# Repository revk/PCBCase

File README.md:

# PCBCase

Now at [Codeberg](https://codeberg.org/RevK/PCBCase)

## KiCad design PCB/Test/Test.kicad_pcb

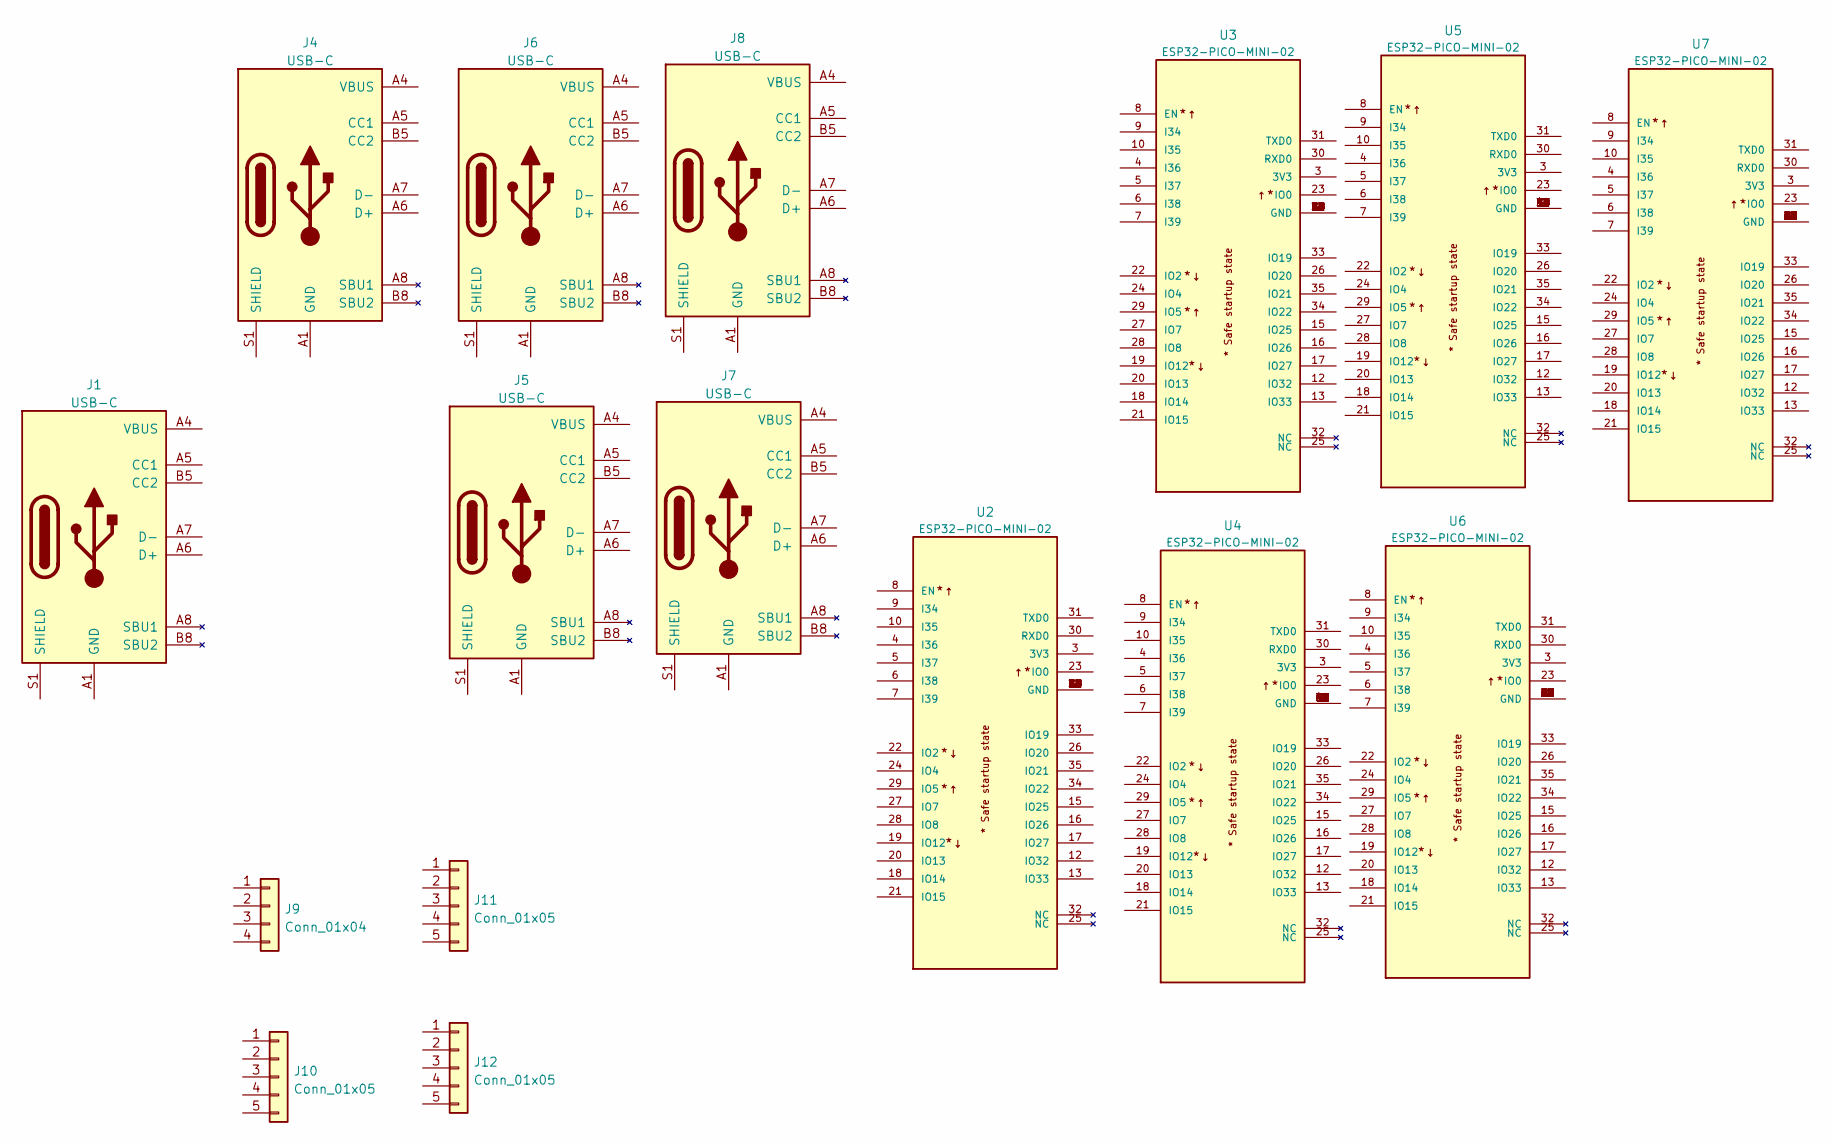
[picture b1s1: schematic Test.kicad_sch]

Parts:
J1, J4, J5, J6, J7, J8: USB-C; USC16-TR-Round
J9: Conn_01x04; JLC-PinHeader_1x04_P2.54mm_Right
J10: Conn_01x05; PTSM-HH-5-RA-P
J11: Conn_01x05; PTSM-HH-5-RA
J12: Conn_01x05; PTSM-HH-5-RA-P-SMD
U2, U3, U4, U5, U6, U7: ESP32-PICO-MINI-02; PARTREV v1.0

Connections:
unnamed: J1.A1 (GND), J1.A12 (GND), J1.B1 (GND), J1.B12 (GND)
unnamed: J1.A4 (VBUS), J1.A9 (VBUS), J1.B4 (VBUS), J1.B9 (VBUS)
unnamed: J1.A6 (D+), J1.B6 (D+)
unnamed: J1.A7 (D-), J1.B7 (D-)
unnamed: J4.A1 (GND), J4.A12 (GND), J4.B1 (GND), J4.B12 (GND)
unnamed: J4.A4 (VBUS), J4.A9 (VBUS), J4.B4 (VBUS), J4.B9 (VBUS)
unnamed: J4.A6 (D+), J4.B6 (D+)
unnamed: J4.A7 (D-), J4.B7 (D-)
unnamed: J5.A1 (GND), J5.A12 (GND), J5.B1 (GND), J5.B12 (GND)
unnamed: J5.A4 (VBUS), J5.A9 (VBUS), J5.B4 (VBUS), J5.B9 (VBUS)
unnamed: J5.A6 (D+), J5.B6 (D+)
unnamed: J5.A7 (D-), J5.B7 (D-)
unnamed: J6.A1 (GND), J6.A12 (GND), J6.B1 (GND), J6.B12 (GND)
unnamed: J6.A4 (VBUS), J6.A9 (VBUS), J6.B4 (VBUS), J6.B9 (VBUS)
unnamed: J6.A6 (D+), J6.B6 (D+)
unnamed: J6.A7 (D-), J6.B7 (D-)
unnamed: J7.A1 (GND), J7.A12 (GND), J7.B1 (GND), J7.B12 (GND)
unnamed: J7.A4 (VBUS), J7.A9 (VBUS), J7.B4 (VBUS), J7.B9 (VBUS)
unnamed: J7.A6 (D+), J7.B6 (D+)
unnamed: J7.A7 (D-), J7.B7 (D-)
unnamed: J8.A1 (GND), J8.A12 (GND), J8.B1 (GND), J8.B12 (GND)
unnamed: J8.A4 (VBUS), J8.A9 (VBUS), J8.B4 (VBUS), J8.B9 (VBUS)
unnamed: J8.A6 (D+), J8.B6 (D+)
unnamed: J8.A7 (D-), J8.B7 (D-)
unnamed: U2.1 (GND), U2.2 (GND), U2.11 (GND), U2.14 (GND), U2.36 (GND), U2.37 (GND), U2.38 (GND), U2.39 (GND), U2.40 (GND), U2.41 (GND), U2.42 (GND), U2.43 (GND), U2.44 (GND), U2.45 (GND), U2.46 (GND), U2.47 (GND), U2.48 (GND), U2.49 (GND), U2.50 (GND), U2.51 (GND), U2.52 (GND), U2.53 (GND)
unnamed: U3.1 (GND), U3.2 (GND), U3.11 (GND), U3.14 (GND), U3.36 (GND), U3.37 (GND), U3.38 (GND), U3.39 (GND), U3.40 (GND), U3.41 (GND), U3.42 (GND), U3.43 (GND), U3.44 (GND), U3.45 (GND), U3.46 (GND), U3.47 (GND), U3.48 (GND), U3.49 (GND), U3.50 (GND), U3.51 (GND), U3.52 (GND), U3.53 (GND)
unnamed: U4.1 (GND), U4.2 (GND), U4.11 (GND), U4.14 (GND), U4.36 (GND), U4.37 (GND), U4.38 (GND), U4.39 (GND), U4.40 (GND), U4.41 (GND), U4.42 (GND), U4.43 (GND), U4.44 (GND), U4.45 (GND), U4.46 (GND), U4.47 (GND), U4.48 (GND), U4.49 (GND), U4.50 (GND), U4.51 (GND), U4.52 (GND), U4.53 (GND)
unnamed: U5.1 (GND), U5.2 (GND), U5.11 (GND), U5.14 (GND), U5.36 (GND), U5.37 (GND), U5.38 (GND), U5.39 (GND), U5.40 (GND), U5.41 (GND), U5.42 (GND), U5.43 (GND), U5.44 (GND), U5.45 (GND), U5.46 (GND), U5.47 (GND), U5.48 (GND), U5.49 (GND), U5.50 (GND), U5.51 (GND), U5.52 (GND), U5.53 (GND)
unnamed: U6.1 (GND), U6.2 (GND), U6.11 (GND), U6.14 (GND), U6.36 (GND), U6.37 (GND), U6.38 (GND), U6.39 (GND), U6.40 (GND), U6.41 (GND), U6.42 (GND), U6.43 (GND), U6.44 (GND), U6.45 (GND), U6.46 (GND), U6.47 (GND), U6.48 (GND), U6.49 (GND), U6.50 (GND), U6.51 (GND), U6.52 (GND), U6.53 (GND)
unnamed: U7.1 (GND), U7.2 (GND), U7.11 (GND), U7.14 (GND), U7.36 (GND), U7.37 (GND), U7.38 (GND), U7.39 (GND), U7.40 (GND), U7.41 (GND), U7.42 (GND), U7.43 (GND), U7.44 (GND), U7.45 (GND), U7.46 (GND), U7.47 (GND), U7.48 (GND), U7.49 (GND), U7.50 (GND), U7.51 (GND), U7.52 (GND), U7.53 (GND)

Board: 11 copper layers, 16 parts (6 on the bottom side), 30 nets, no tracks yet.

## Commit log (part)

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2024-01-20 More
2024-01-20 Try that
2024-01-20 Rotate
2024-01-20 LGA-16_3x3mm_P0.5mm_LayoutBorder3x5y
2024-01-20 new part
2024-01-20 More space
2024-01-20 Better
2024-01-20 Again
2024-06-16 Messages
2024-06-20 Update for later kiCAD
2024-06-20 Reference
2024-06-20 More parts
2024-06-20 hole
2024-06-20 centre
2024-06-20 Clash
2024-06-30 Tweak to avoid clash
2024-07-13 1x1 RGB
2024-07-28 New bits
2024-07-28 Screws
2024-07-28 Turn
2024-07-28 FFS reverted
2024-07-28 Clearance
2024-07-28 Was so tight it killed LEDs
2024-07-28 Bigger
2024-07-28 Wider
2024-07-28 Try to remove scad errors
2024-07-28 Back
2024-08-11 WAGO
2024-08-11 Set n
2024-08-11 Position
2024-08-11 Wires
2025-01-04 New models
2025-01-12 Working on clean code
2025-01-12 Started render logic
2025-01-12 New render tools
2025-01-12 rectangles
2025-01-12 README
2025-01-12 Make readme
2025-01-12 Clean
2025-01-12 Indent
2025-01-12 Autocrop
2025-01-12 Working on QR
2025-01-12 NO idf
2025-01-12 Higher res
2025-01-12 Zoom
2025-01-12 Quality high
2025-01-12 Back SS QR
2025-01-13 Transparent
2025-01-13 Alt (User.4)
2025-01-17 More images
2025-01-18 Better readme
2025-01-18 Debug
2025-01-19 Remake
2025-01-19 Tidy
2025-01-19 Auto
2025-01-30 Added datamatrix (not used yet)
2025-01-30 Started DM
2025-01-30 DM working
2025-01-30 Add datamatrix
2025-02-12 Side
2025-02-15 typo
2025-02-15 DM fix
2025-02-15 Formatting
2025-02-15 Floats
2025-02-27 Not working yet
2025-04-19 Higher
2025-04-19 3mm is actually enough
2025-04-22 Format
2025-04-22 edge in DNP still exists
2025-04-22 Switch
2025-04-23 Pillar
2025-04-23 Non SMD
2025-04-25 Library update
2025-04-25 Better errors
2025-04-25 Tweak
2025-04-25 Side ways
2025-04-26 oTweaks
2025-04-26 down hole
2025-05-02 Model tidy
2025-05-02 Rework
2025-05-04 Fine tuning
2025-05-05 Try switch size
2025-05-11 new options origin and parts
2025-05-12 Tweaks
2025-05-12 D'Oh
2025-05-12 S'Oh
2025-05-17 Push
2025-05-24 LiPo1
2025-05-31 Clean up
2025-05-31 Thicker
2025-05-31 Block
2025-06-02 Spacing
2025-06-02 Adjust edge hole logic
2025-06-02 Temp sensor
2025-06-02 Tidy case
2025-06-03 Which side
2025-06-03 Try to remove thin edges
2025-08-01 5x5x4
2025-08-01 0201
2025-08-01 SOT-563
2025-08-04 Double lip
2025-08-04 New defaults
2025-08-04 Back to 2 now
2025-08-09 Two way cut
2025-08-09 Lip fix
2025-08-09 Lip tidy
2025-08-09 Allow top/bottom only
2025-08-10 Button
2025-08-10 Redo
2025-08-10 Tidy hold
2025-08-11 Fit adjust
2025-08-11 Adjust edges
2025-08-11 messy
2025-08-11 PCB edges
2025-08-11 Fit and snap
2025-08-11 Margins
2025-08-11 Fit fix
2025-08-12 Correct size
2025-08-12 Match data sheet
2025-08-12 include and liptype
2025-08-12 Tweak, oddly an F5 render does not show the holes?
2025-08-12 Lip-type
2025-08-12 Snap design change
2025-08-12 Defaults
2025-08-12 Dual file
2025-08-12 New bridgeed lip logic
2025-08-12 Adjusted S interlocks
2025-08-13 Use ℕ
2025-08-13 debug removed
2025-08-13 WAGO -S
2025-08-13 Smaller
2025-08-15 Clearance for small print
2025-08-15 Neater holes
2025-08-15 Tidy holes
2025-08-18 Pin hole
2025-08-18 Change snap default for resin
2025-08-18 Allow more for pins
2025-08-20 Slight margin increase
2025-08-24 Date code
2025-08-24 Date
2025-08-24 Right way around
2025-08-24 Font
2025-08-24 Edge
2025-08-25 headers
2025-08-25 datea
2025-08-25 README script
2025-08-25 List KiCAD
2025-08-25 Avoid issues
2025-08-25 Avoid clash with */*.scad make
2025-08-25 Datecode tidy
2025-09-03 Add parts
2025-09-03 All footptints
2025-09-08 functions to get thickness/width
2025-09-08 MicroSD
2025-09-08 Finger size
2025-09-14 Testing
2025-09-14 More tweaks
2025-09-14 Case
2025-09-14 Posts
2025-09-16 Cover
2025-09-16 Back/fcront block
2025-09-16 Cleaner block
2025-09-16 MOre fixes
2025-09-16 Battey size
2025-09-16 Slivers
2025-09-16 Smaller holes
2025-09-16 sliver
2025-09-17 Adjust
2025-09-17 Fix position
2025-09-18 Holes
2025-09-18 Tidy block
2025-09-21 Alt hole logic
2025-09-25 Add esphome-toshiba-ab parts
2025-09-26 Fix esphome-toshiba-ab parts
2025-09-27 Add Docker and Docker Compose support
2025-09-27 (docker) Upgrade to latest SNAPSHOT version of OpenSCAD
2025-09-28 Bigger LEDs
2025-09-30 --top-thickness / --bottom-thickness
2025-10-01 Add png
2025-10-01 STL render
2025-10-01 try taht
2025-10-01 8FFS
2025-10-01 Cleaner
2025-10-01 Space
2025-10-01 Title
2025-10-01 Antialias
2025-10-06 Margin tweak
2025-10-07 Blind LED
2025-10-09 Added placeleds
2025-10-09 new LEDs
2025-10-10 Bigger hole
2025-10-12 Thick walls
2025-10-12 Clean up to match part better
2025-10-12 Tidy more
2025-10-19 Combined
2025-10-26 Manifold fix
2025-10-30 Logo on top
2025-10-30 Margin
2025-10-30 Logo
2025-11-05 Colour
2025-11-05 WhiteResin scheme
2025-11-08 More on grid LEDs
2025-11-09 Clean up grid
2025-11-20 More models
2025-11-27 Card not PCb
2025-11-29 hole for card
2025-12-01 Slot
2025-12-01 Parts bottom
2025-12-03 Push through
2026-01-03 Handle casework better
2026-01-03 Corrected shape
2026-01-03 Side cuts
2026-01-18 Spring
2026-01-18 Error in height
2026-01-18 Name field
2026-01-18 Size
2026-01-26 Square end
2026-01-31 New model
2026-01-31 Extra side
